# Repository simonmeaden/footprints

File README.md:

# footprints
My KICAD footprint library

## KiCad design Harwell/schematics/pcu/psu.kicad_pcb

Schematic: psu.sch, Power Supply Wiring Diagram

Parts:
C1: 2.2uF; CP_Elec_6.3x7.7
C2, C11, C13, C21: 2.2uF; C_0805
C3: 6800pF; C_0805
C4, C18, C24: 0.1uF; C_0805
C5: 3900pF; C_0805
C6, C14: 150uF; CP_Elec_6.3x7.7
C7, C9, C10, C15, C16, C23, C29: 0.01uF; C_0805
C8, C17: TBD; C_0805
C12: 22uF; C_0805
C19: 3300pF; C_0805
C20: 2200pF; C_0805
C25, C31: 100uF; CP_Tantalum_Case-X_EIA-7343-43_Reflow
C26, C36: 10uF; CP_Tantalum_Case-B_EIA-3528-21_Reflow
C27, C37: 1uF; CP_Tantalum_Case-A_EIA-3216-18_Reflow
C32: 22uF Tantalum; CP_Tantalum_Case-B_EIA-3528-21_Reflow
D1: MBR630; D_SOD-123
D2: MBR530; D_SOD-123
JP5: Jumper 5; SOLDER-JUMPER_2-WAY
L1, L2: 4uH; Inductor_Murata_3900_Series
L3, L4: 100uH; Inductor_TDK_VLCF5020_Series
L6: 22uH; Inductor_TDK__SLF_Series
M4: B240
Q1, Q6: FDS6612A
Q2, Q3, Q4, Q5: FDS6690AS
R1, R16: 15R; R_0805
R2, R3, R4, R17: 100K; R_0805
R5: 49K7; R_0805
R6: 1K8; R_0805
R7, R13: 330R; R_0805
R8, R12: 10K; R_0805
R9, R11: 18K2; R_0805
R10: 3R92; R_0805
R14: 2K7; R_0805
R15: 28K8; R_0805
R31: 20R; Potentiometer_Bourns_3362P
SKT1: CONN_01X02; CTBP9558_2AO
SKT2: LM2N_3.5_16; LM2N_16_2
TP1, TP2, TP3, TP4, TP5, TP6, TP7: TEST; Measurement_Point_Square-TH_Big
U3: MAX743; SO-16-W; Part Number IC000005
U5: CAT4139; TSOT-23-5; Part Number IC000007
U$3: TPD51020; TSSOP30

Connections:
+3V3: C14.1, C15.1, C20.2, L2.2, R15.2, SKT2.5, SKT2.6, SKT2.7, SKT2.8, TP4.1, U$3.11 (VO2)
+5V: C3.1, C6.1, C7.1, C24.1, C32.1, C36.1, JP5.3 (G3), L1.2, L3.1, L6.1, R5.1, SKT2.1, SKT2.2, SKT2.3, SKT2.4, TP2.1, U3.3 (AV+), U3.4 (V+), U3.5 (V+), U3.12 (V+), U3.13 (V+), U5.4 (~SHDN~), U5.5 (VIN), U$3.5 (VO1_VDDQ), U$3.21 (REG5_IN)
/DCIN: C1.1, C2.1, C12.1, C21.2, Q1.D, Q6.D, R2.1, R3.1, R4.1, R10.2, SKT1.1, TP1.1
/GND+12V: C31.2, D2.2 (A), SKT2.10, TP6.1, U3.9 (FB-)
/LL1: C4.1, L1.1, Q1.S, Q2.D, Q3.D, U$3.28 (LL1)
/LL2: C18.2, L2.1, Q4.D, Q5.D, Q6.S, U$3.18 (LL2)
/N$54: Q2.G, Q3.G, U$3.27 (OUT1_D)
/N$58: Q4.G, Q5.G, U$3.19 (OUT2_D)
/OUT1_U: Q1.G, R1.2
/OUT2_U: Q6.G, R16.2
/VDD+12.0: C25.1, D1.1 (K), SKT2.9, TP5.1, U3.16 (FB+)
/VDDLCD+: C37.1, M4.C, SKT2.11, TP7.1
GND: C1.2, C2.2, C6.2, C7.2, C9.1, C10.1, C11.2, C12.2, C13.1, C14.2, C15.2, C16.1, C21.1, C23.2, C24.2, C25.2, C26.2, C27.2, C29.2, C31.1, C32.2, C36.2, C37.2, JP5.1 (G1), L4.2, Q2.S, Q3.S, Q4.S, Q5.S, R8.1, R12.1, R31.2, SKT1.2, SKT2.12, SKT2.13, SKT2.14, SKT2.15, SKT2.16, TP3.1, U3.2 (AGND), U3.14 (GND), U5.2 (GND), U$3.4 (~SKIP~), U$3.7 (GND), U$3.20 (OUTGND2), U$3.26 (OUTGND1)
unnamed: C3.2, R7.1
unnamed: C4.2, U$3.30 (VBST1)
unnamed: C5.1, R5.2, R7.2, R8.2, U$3.1 (INV1)
unnamed: C5.2, R6.1
unnamed: C8.1, R9.1, U$3.25 (TRIP1)
unnamed: C9.2, U$3.3 (SSTRT1)
unnamed: C10.2, U$3.8 (REF_X)
unnamed: C8.2, C11.1, C17.2, R9.2, R10.1, R11.2, U$3.24 (VIN)
unnamed: C13.2, R17.2, U$3.22 (VREG5)
unnamed: C16.2, U$3.13 (SSTRT2)
unnamed: C17.1, R11.1, U$3.23 (TRIP2)
unnamed: C18.1, U$3.16 (VBST2)
unnamed: C19.1, R12.2, R13.1, R15.1, U$3.15 (INV2)
unnamed: C19.2, R14.1
unnamed: C20.1, R13.2
unnamed: C23.1, U3.1 (CC+)
unnamed: C26.1, U3.6 (VREF)
unnamed: C27.1, U3.7 (SS)
unnamed: C29.1, U3.8 (CC-)
unnamed: D1.2 (A), L3.2, U3.15 (LX+)
unnamed: D2.1 (K), L4.1, U3.10 (LX-)
unnamed: JP5.2 (G2), U3.11 (12/~15~)
unnamed: L6.2, M4.A, U5.1 (SW)
unnamed: R1.1, U$3.29 (OUT1_U)
unnamed: R2.2, U$3.10 (ENBL2)
unnamed: R3.2, U$3.9 (ENBL1)
unnamed: R4.2, U$3.6 (~DDR~)
unnamed: R6.2, U$3.2 (COMP1)
unnamed: R14.2, U$3.14 (COMP2)
unnamed: R16.1, U$3.17 (OUT2_U)
unnamed: R17.1, U$3.12 (PGOOD)
unnamed: R31.1, U5.3 (FB)

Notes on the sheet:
∓12V @ 125mA.Supply for DAC Buffer ampifier to avoid output Signal approaching either power rail.
Resistor R18 sets output voltage. 9.3V = 13R7
For Display LED Backlight.
Primary 5.0V & 3.3V Power supply.
DAC Buffer amp PSU
Display Backlight PSU
JP5 : 2-3 Connect for +12V 1-2 Connect for +15V

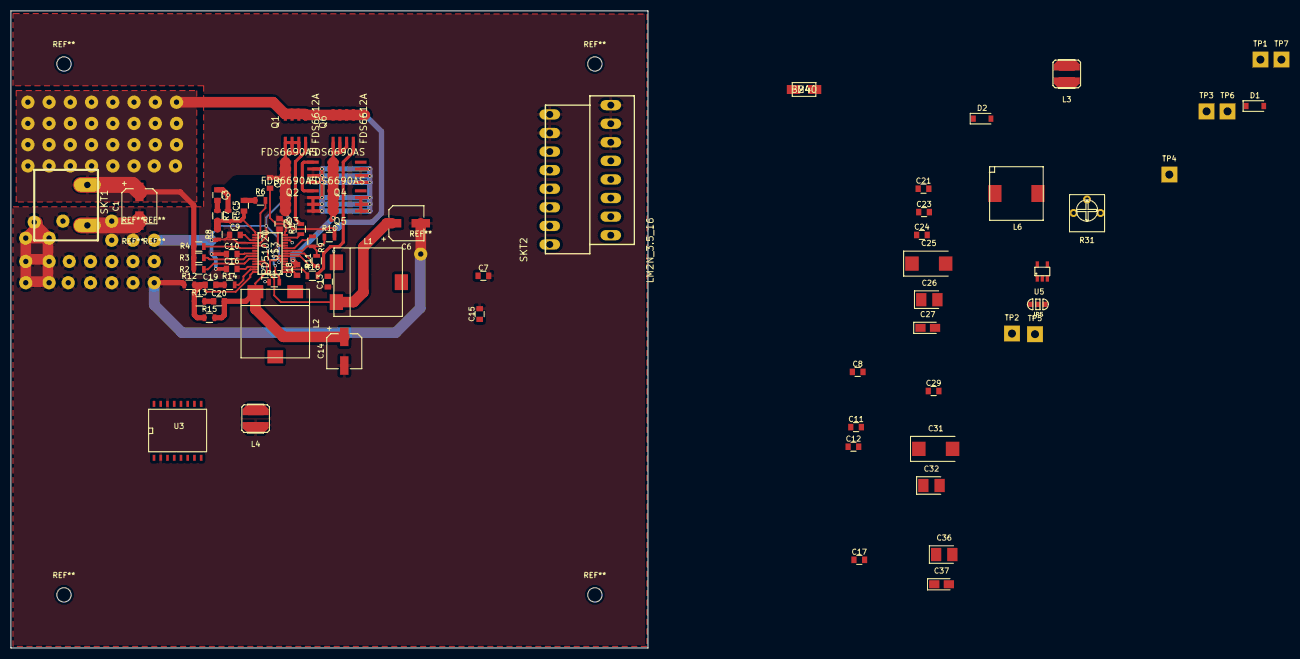
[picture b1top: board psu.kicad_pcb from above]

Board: 4 copper layers, 120.0 x 120.0 mm, 76 parts (0 on the bottom side), 43 nets.

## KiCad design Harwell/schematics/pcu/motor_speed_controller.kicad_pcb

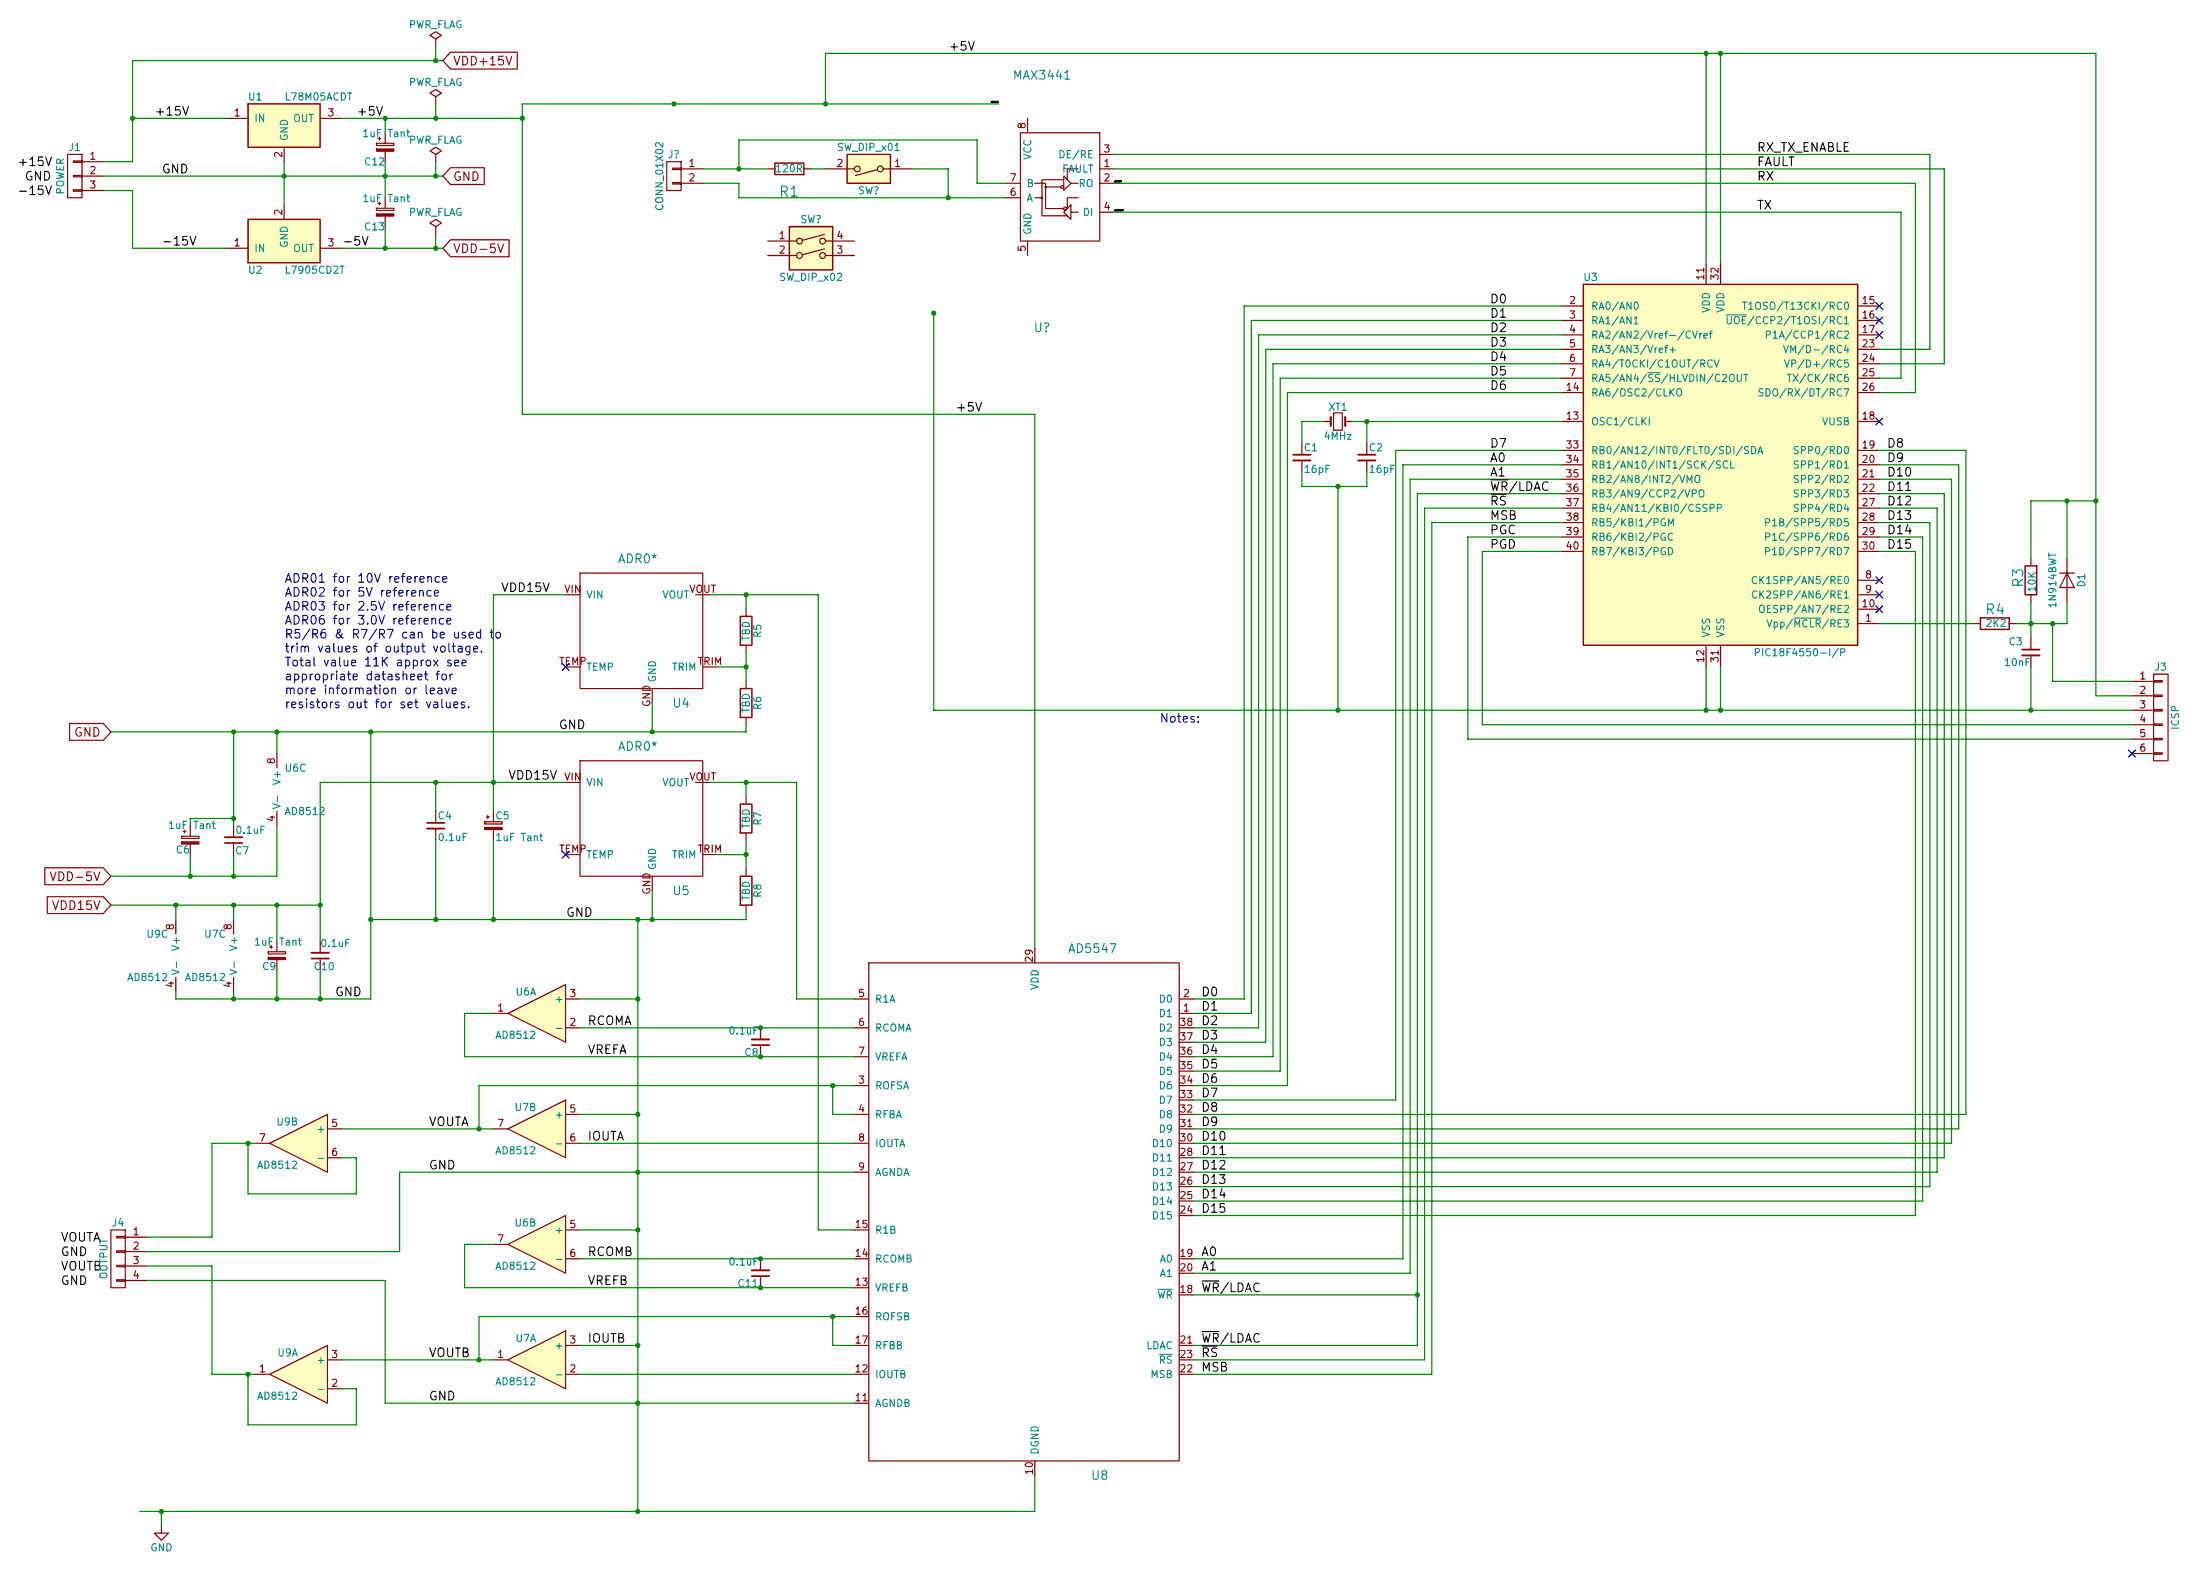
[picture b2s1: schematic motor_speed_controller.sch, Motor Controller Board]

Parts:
C1, C2: 16pF; C_0805
C3: 10nF; C_0805
C4, C7, C8, C10, C11: 0.1uF; C_0805
C5, C6, C9, C12, C13: 1uF Tant; CP_Tantalum_Case-A_EIA-3216-18_Reflow
D1: 1N914BWT; D_SOD-523F
J1: POWER; CTBP9558_3AO
J3: ICSP; Molex_KK_6373-06_06x2.54mm_Straight
J4: OUTPUT; CTBP9558_4AO
R1: 120R; R_0805
R3: 10K; R_0805
R4: 2K2; R_0805
R5, R6, R7, R8: TBD; R_0805
U1: L78M05ACDT; TO-252-2Lead_L778M05ACDT
U2: L7905CD2T; TO-252-2Lead_L7905CD2T
U3: PIC18F4550-I/P; DIP-40_W15.24mm
U4, U5: ADR0*; TSOT-5-ADR0*
U6, U7: AD8512; SOIC-8-N
U8: AD5547; TSSOP38
U9: AD8512
XT1: 4MHz; Crystal_IQD_HC49-4HSMX

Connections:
/+5V: C12.1, D1.1 (K), J3.2, R3.2, U1.3 (OUT), U3.11 (VDD), U3.32 (VDD), U8.29 (VDD); also elsewhere on the board
/-15V: J1.3, U2.1 (IN)
/A0: U3.34 (RB1/AN10/INT1/SCK/SCL), U8.19 (A0)
/A1: U3.35 (RB2/AN8/INT2/VMO), U8.20 (A1)
/D0: U3.2 (RA0/AN0), U8.2 (D0)
/D1: U3.3 (RA1/AN1), U8.1 (D1)
/D2: U3.4 (RA2/AN2/Vref-/CVref), U8.38 (D2)
/D3: U3.5 (RA3/AN3/Vref+), U8.37 (D3)
/D4: U3.6 (RA4/T0CKI/C1OUT/RCV), U8.36 (D4)
/D5: U3.7 (RA5/AN4/~SS~/HLVDIN/C2OUT), U8.35 (D5)
/D6: U3.14 (RA6/OSC2/CLKO), U8.34 (D6)
/D7: U3.33 (RB0/AN12/INT0/FLT0/SDI/SDA), U8.33 (D7)
/D8: U3.19 (SPP0/RD0), U8.32 (D8)
/D9: U3.20 (SPP1/RD1), U8.31 (D9)
/D10: U3.21 (SPP2/RD2), U8.30 (D10)
/D11: U3.22 (SPP3/RD3), U8.28 (D11)
/D12: U3.27 (SPP4/RD4), U8.27 (D12)
/D13: U3.28 (P1B/SPP5/RD5), U8.26 (D13)
/D14: U3.29 (P1C/SPP6/RD6), U8.25 (D14)
/D15: U3.30 (P1D/SPP7/RD7), U8.24 (D15)
/DATAIN: U3.26 (SDO/RX/DT/RC7); also elsewhere on the board
/DATAOUT: U3.25 (TX/CK/RC6); also elsewhere on the board
/IOUTA: U7.6 (-), U8.8 (IOUTA)
/MSB: U3.38 (RB5/KBI1/PGM), U8.22 (MSB)
/N$9: R1.2; also elsewhere on the board
/N$16: R1.1; also elsewhere on the board
/PGC: J3.5, U3.39 (RB6/KBI2/PGC)
/PGD: J3.4, U3.40 (RB7/KBI3/PGD)
/RCOMA: C8.2, U6.2 (-), U8.6 (RCOMA)
/RCOMB: C11.2, U6.6 (-), U8.14 (RCOMB)
/RX_ENABLE: U3.24 (VP/D+/RC5); also elsewhere on the board
/TX_ENABLE: U3.23 (VM/D-/RC4); also elsewhere on the board
/VOUTA: J4.1, U7.7, U8.3 (ROFSA), U8.4 (RFBA), U9.5 (+), U9.6 (-), U9.7
/VOUTB: J4.3, U7.1, U8.16 (ROFSB), U8.17 (RFBB), U9.1, U9.2 (-), U9.3 (+)
/VREFA: C8.1, U6.1, U8.7 (VREFA)
/VREFB: C11.1, U6.7, U8.13 (VREFB)
/~RS~: U3.37 (RB4/AN11/KBI0/CSSPP), U8.23 (~RS~)
/~WR~/LDAC: U3.36 (RB3/AN9/CCP2/VPO), U8.18 (~WR~), U8.21 (LDAC)
unnamed: C1.1, XT1.1
unnamed: C2.1, U3.13 (OSC1/CLKI), XT1.2
unnamed: C3.1, D1.2 (A), J3.1, R3.1, R4.1
unnamed: R4.2, U3.1 (Vpp/~MCLR~/RE3)
unnamed: R5.1, U4.VOUT, U8.15 (R1B)
unnamed: R5.2, R6.1, U4.TRIM
unnamed: R7.1, U5.VOUT, U8.5 (R1A)
unnamed: R7.2, R8.1, U5.TRIM
unnamed: U7.2 (-), U8.12 (IOUTB)
VDD15V: C4.1, C5.1, C9.1, C10.2, U4.VIN, U5.VIN, U7.8 (V+), U9.8 (V+)
VDD+15V: J1.1, U1.1 (IN)
VDD-5V: C6.2, C7.1, C13.2, U2.3 (OUT), U6.4 (V-)

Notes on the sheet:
Notes:
ADR01 for 10V reference ADR02 for 5V reference ADR03 for 2.5V reference ADR06 for 3.0V reference R5/R6 & R7/R7 can be used to trim values of output voltage. Total value 11K approx see appropriate datasheet for more information or leave resistors out for set values.

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
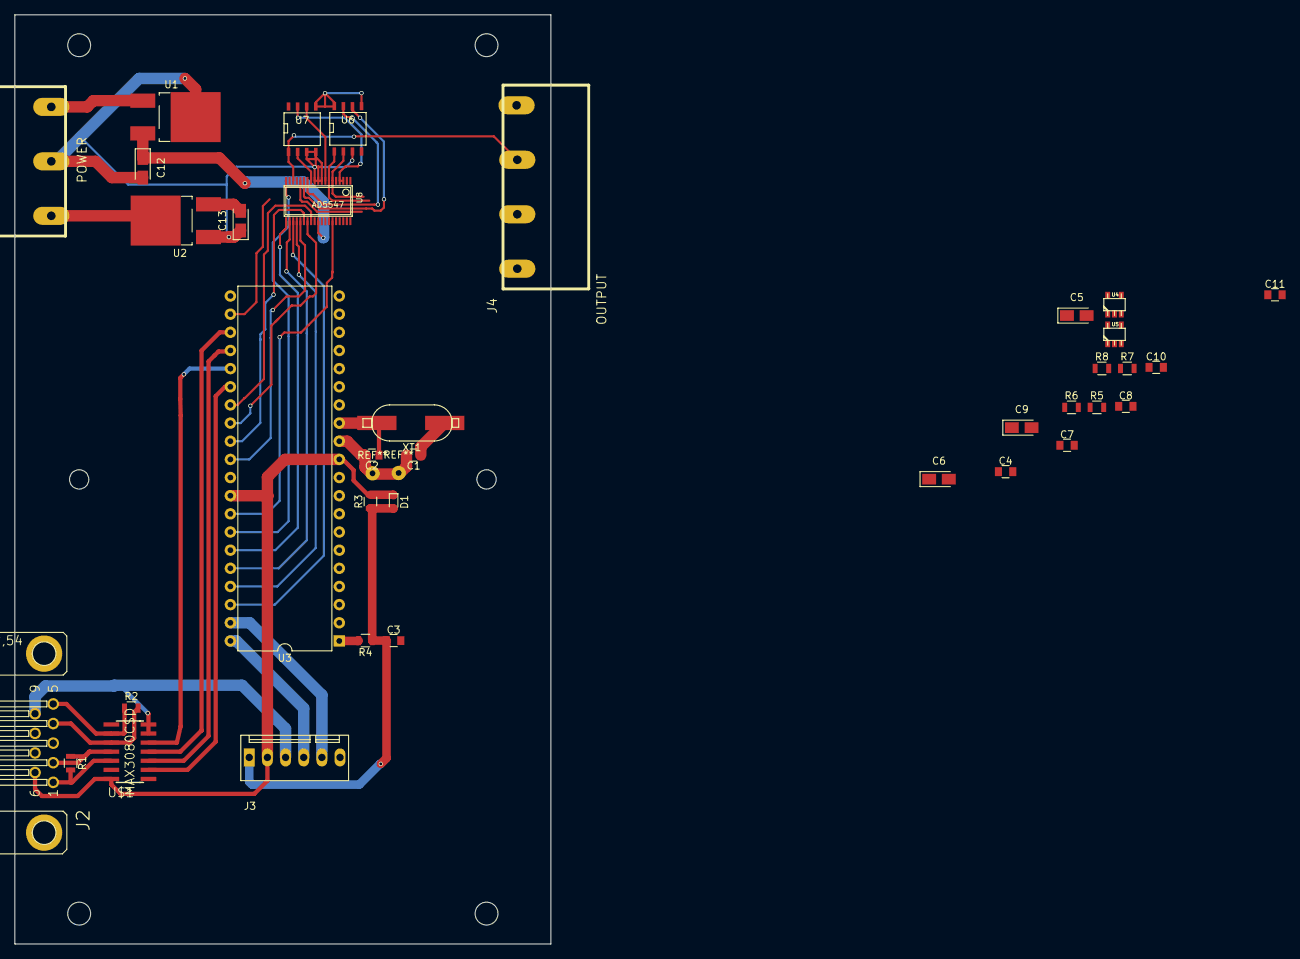
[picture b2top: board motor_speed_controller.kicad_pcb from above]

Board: 2 copper layers, 75.0 x 130.0 mm, 36 parts (0 on the bottom side), 53 nets.

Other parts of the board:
J2: RS485; F09HP
R2: 120R; R_0805
U$1: MAX3080CSD; SO14

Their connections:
/+5V: J2.6, U$1.14; also elsewhere on the board
/DATAIN: U$1.2; also elsewhere on the board
/DATAOUT: U$1.5; also elsewhere on the board
/N$9: J2.1, U$1.12; also elsewhere on the board
/N$16: J2.2, U$1.11; also elsewhere on the board
/N$17: J2.4, R2.2, U$1.10
/N$18: J2.5, R2.1, U$1.9
/RX_ENABLE: U$1.3; also elsewhere on the board
/TX_ENABLE: U$1.4; also elsewhere on the board

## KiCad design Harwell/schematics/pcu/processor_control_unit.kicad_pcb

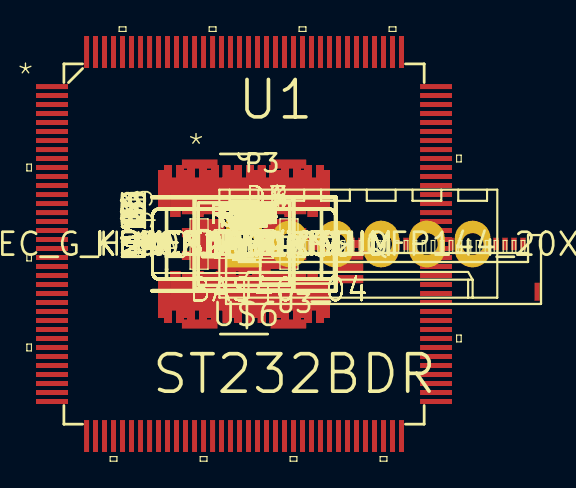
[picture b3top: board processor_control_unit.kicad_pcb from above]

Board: 2 copper layers, 219 parts (0 on the bottom side), 166 nets, no tracks yet.

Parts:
C4, C5: 18pF; C_0603
C6, C7, C8, C10, C11, C12, C13, C14: 0.1uF; C_0603
C9: 0.01uF; C_0603
D1, D2, D3, D4, D5: BAS40-04; SOT23
IC1, IC2, IC3, IC4, IC5, IC6, IC7, IC8: MCP23017SS; SSOP28
M1, M2, M3, M4, M5, M6, M7, M8, M9, M10, M11, M12, M13, M14, M15, M16: ACSL-6400; SO16
P1: CONN_01X32; 503480-3200
P3: CONN_01X06; Molex_KK-6410-06_06x2.54mm_Straight
R11, R12: 120R; R_0603
R17, R18, R19, R20, R25, R26, R27, R28, R49, R50, R51, R52, R57, R58, R59, R60, R133, R134, R135, R136, R141, R142, R143, R144, R165, R166, R167, R168, R173, R174, R175, R176, R197, R198, R199, R200, R205, R206, R207, R208, R229, R230, R231, R232, R237, R238, R239, R240, R261, R262, R263, R264, R269, R270, R271, R272, R293, R294, R295, R296, R301, R302, R303, R304: 147R; R_0805
R81, R83, R85, R90, R92, R94, R99, R101, R108, R110, R112, R117, R119, R123, R125, R325, R327, R329, R334, R336, R338, R343, R345, R352, R354, R356, R361, R363, R367, R369: 33K; R_0805
R82, R84, R86, R91, R93, R95, R100, R102, R104, R109, R111, R113, R118, R120, R124, R126, R326, R328, R330, R335, R337, R339, R344, R346, R348, R353, R355, R357, R362, R364, R368, R370: 3K3; R_0805
R87, R88, R89, R96, R97, R98, R105, R106, R107, R114, R115, R116, R121, R122, R127, R128, R331, R332, R333, R340, R341, R342, R349, R350, R351, R358, R359, R360, R365, R366, R371, R372: 10K; R_0805
R103, R347: R33K; R_0805
R129: 10K0; R_0805
R130: 1K0; R_0805
R131, R132: 2K7; R_0805
U1: ST232BDR; SOIC127P600X175-16N
U2, U4: CA3130; SOIC-8-N
U3: MCP47FEB22A0; TSSOP8
U9: PIC32MZXXXXEC_G_H_M_144-I_PLLQFP144_20X20MC-M; LQFP144_20X20MC-M
U$1, U$2, U$3, U$4: KEMET_AMAXIMUM; 3216-18W
U$5: MAX3080CSD; SO14
U$6: 2.2Uh; Inductor_Vishay_IHLP-2020BZ-11_Series

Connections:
/485-RX+: R11.2, U$5.12
/485-RX-: R11.1, U$5.11
/485-TX+: R12.2, U$5.10
/485-TX-: R12.1, U$5.9
/Analogue Inputs/AD0: D1.3, U9.36
/Analogue Inputs/AD1: D2.3, U9.35
/Analogue Inputs/AD2: D3.3, U9.34
/Analogue Inputs/AD3: D4.3, U9.31
/Analogue Inputs/AD4: D5.3, U9.26
/Dual DAC/LATCH/HVC: U3.6, U9.1
/INT-1: IC3.19, IC3.20, U9.79
/INT-2: IC5.19, IC5.20, U9.80
/INT-3: IC6.19, IC6.20, U9.106
/INT-4: IC7.19, IC7.20, U9.105
/Opto Isolated Inputs 1/CH0: IC3.21, M1.14
/Opto Isolated Inputs 1/CH1: IC3.22, M1.13
/Opto Isolated Inputs 1/CH2: IC3.23, M1.12
/Opto Isolated Inputs 1/CH3: IC3.24, M1.11
/Opto Isolated Inputs 1/CH4: IC3.25, M3.14
/Opto Isolated Inputs 1/CH5: IC3.26, M3.13
/Opto Isolated Inputs 1/CH6: IC3.27, M3.12
/Opto Isolated Inputs 1/CH7: IC3.28, M3.11
/Opto Isolated Inputs 1/CH11: IC3.4, M2.11
/Opto Isolated Inputs 1/CH13: IC3.6, M4.13
/Opto Isolated Inputs 1/CH14: IC3.7, M4.12
/Opto Isolated Inputs 1/CH15: IC3.8, M4.11
/Opto Isolated Inputs 2/CH0: IC5.21, M5.14
/Opto Isolated Inputs 2/CH1: IC5.22, M5.13
/Opto Isolated Inputs 2/CH2: IC5.23, M5.12
/Opto Isolated Inputs 2/CH3: IC5.24, M5.11
/Opto Isolated Inputs 2/CH4: IC5.25, M7.14
/Opto Isolated Inputs 2/CH5: IC5.26, M7.13
/Opto Isolated Inputs 2/CH6: IC5.27, M7.12
/Opto Isolated Inputs 2/CH7: IC5.28, M7.11
/Opto Isolated Inputs 2/CH11: IC5.4, M6.11
/Opto Isolated Inputs 2/CH13: IC5.6, M8.13
/Opto Isolated Inputs 2/CH14: IC5.7, M8.12
/Opto Isolated Inputs 2/CH15: IC5.8, M8.11
/Opto Isolated Inputs 3/CH0: IC6.21, M9.14
/Opto Isolated Inputs 3/CH1: IC6.22, M9.13
/Opto Isolated Inputs 3/CH2: IC6.23, M9.12
/Opto Isolated Inputs 3/CH3: IC6.24, M9.11
/Opto Isolated Inputs 3/CH4: IC6.25, M11.14
/Opto Isolated Inputs 3/CH5: IC6.26, M11.13
/Opto Isolated Inputs 3/CH6: IC6.27, M11.12
/Opto Isolated Inputs 3/CH7: IC6.28, M11.11
/Opto Isolated Inputs 3/CH11: IC6.4, M10.11
/Opto Isolated Inputs 3/CH13: IC6.6, M12.13
/Opto Isolated Inputs 3/CH14: IC6.7, M12.12
/Opto Isolated Inputs 3/CH15: IC6.8, M12.11
/Opto Isolated Inputs 4/CH0: IC7.21, M13.14
/Opto Isolated Inputs 4/CH1: IC7.22, M13.13
/Opto Isolated Inputs 4/CH2: IC7.23, M13.12
/Opto Isolated Inputs 4/CH3: IC7.24, M13.11
/Opto Isolated Inputs 4/CH4: IC7.25, M15.14
/Opto Isolated Inputs 4/CH5: IC7.26, M15.13
/Opto Isolated Inputs 4/CH6: IC7.27, M15.12
/Opto Isolated Inputs 4/CH7: IC7.28, M15.11
/Opto Isolated Inputs 4/CH11: IC7.4, M14.11
/Opto Isolated Inputs 4/CH13: IC7.6, M16.13
/Opto Isolated Inputs 4/CH14: IC7.7, M16.12
/Opto Isolated Inputs 4/CH15: IC7.8, M16.11
/PMD5: U9.3, U9.4
/Processor Control Unit/232-RX: U1.12, U9.16
/Processor Control Unit/232-TX: U1.11, U9.15
/Processor Control Unit/232-~CTS~: U1.9, U9.23
/Processor Control Unit/232-~RTS~: U1.10, U9.14
/Processor Control Unit/485-RX: U9.62, U$5.5
/Processor Control Unit/485-TX: U9.61, U$5.2
/Processor Control Unit/485-~RE~: U9.8, U$5.3
/Processor Control Unit/MCLR: P3.1, R130.2, U9.20
/Processor Control Unit/PGEC: P3.5, U9.37
/Processor Control Unit/PGED: P3.4, U9.38
/SCL-1: IC1.12, IC2.12, IC3.12, IC4.12, IC5.12, IC6.12, IC7.12, IC8.12, R131.1, U3.7, U9.90, U9.96
/SDA-1: IC3.13, R132.1, U9.91, U9.95
/SDA-2: IC1.13, IC2.13, IC4.13, IC5.13, IC6.13, IC7.13, IC8.13, U3.8
/Transistor buffered output 1/T0: IC4.21, R87.1
/Transistor buffered output 1/T1: IC4.22, R96.1
/Transistor buffered output 1/T2: IC4.23, R105.1
/Transistor buffered output 1/T3: IC4.24, R114.1
/Transistor buffered output 1/T4: IC4.25, R121.1
/Transistor buffered output 1/T5: IC4.26, R127.1
/Transistor buffered output 1/T6: IC4.27, R88.1
/Transistor buffered output 1/T7: IC4.28, R97.1
/Transistor buffered output 1/T8: IC4.1, R106.1
/Transistor buffered output 1/T9: IC4.2, R115.1
/Transistor buffered output 1/T10: IC4.3, R122.1
/Transistor buffered output 1/T11: IC4.4, R128.1
/Transistor buffered output 1/T12: IC4.5, R89.1
/Transistor buffered output 1/T13: IC4.6, R98.1
/Transistor buffered output 1/T14: IC4.7, R107.1
/Transistor buffered output 1/T15: IC4.8, R116.1
/Transistor buffered output 2/T0: IC8.21, R331.1
/Transistor buffered output 2/T1: IC8.22, R340.1
/Transistor buffered output 2/T2: IC8.23, R349.1
/Transistor buffered output 2/T3: IC8.24, R358.1
/Transistor buffered output 2/T4: IC8.25, R365.1
/Transistor buffered output 2/T5: IC8.26, R371.1
/Transistor buffered output 2/T6: IC8.27, R332.1
/Transistor buffered output 2/T7: IC8.28, R341.1
/Transistor buffered output 2/T8: IC8.1, R350.1
/Transistor buffered output 2/T9: IC8.2, R359.1
/Transistor buffered output 2/T10: IC8.3, R366.1
/Transistor buffered output 2/T11: IC8.4, R372.1
/Transistor buffered output 2/T12: IC8.5, R333.1
/Transistor buffered output 2/T13: IC8.6, R342.1
/Transistor buffered output 2/T14: IC8.7, R351.1
/Transistor buffered output 2/T15: IC8.8, R360.1
GND: C4.1, C5.1, C6.2, C7.2, C8.1, C9.2, C10.1, C11.2, C12.2, C13.2, C14.2, D4.1, D5.1, IC1.10, IC1.16, IC2.15, IC3.10, IC3.15, IC3.17, IC4.10, IC4.15, IC4.16, IC5.10, IC5.17, IC6.10, IC6.15, IC7.10, IC8.10, M1.9, M1.16, M3.9, M3.16, M4.9, M4.16, M5.9, M5.16, M7.9, M7.16, M8.9, M8.16, M9.9, M9.16, M11.9, M11.16, M12.9, M12.16, M13.9, M13.16, M15.9, M15.16, M16.9, M16.16, P3.3, R25.2, R26.2, R27.2, R28.2, R141.2, R142.2, R143.2, R144.2, R205.2, R206.2, R207.2, R208.2, R269.2, R270.2, R271.2, R272.2, U1.15, U3.5, U9.17, U9.32, U9.42, U9.54, U9.63, U9.75, U9.89, U9.108, U9.123, U9.136, U$5.6, U$5.7
unnamed: C4.2, U9.72
unnamed: C5.2, U9.71
unnamed: C9.1, R129.1, R130.1
unnamed: D1.1, D2.1, D3.1
unnamed: M1.1, R17.1
unnamed: M1.3, R18.1
unnamed: M1.5, R19.1
unnamed: M1.7, R20.1
unnamed: M3.1, R49.1
unnamed: M3.3, R50.1
unnamed: M3.5, R51.1
unnamed: M3.7, R52.1
unnamed: M4.1, R57.1
unnamed: M4.3, R58.1
unnamed: M4.5, R59.1
unnamed: M4.7, R60.1
unnamed: M5.1, R133.1
unnamed: M5.3, R134.1
unnamed: M5.5, R135.1
unnamed: M5.7, R136.1
unnamed: M7.1, R165.1
unnamed: M7.3, R166.1
unnamed: M7.5, R167.1
unnamed: M7.7, R168.1
unnamed: M8.1, R173.1
unnamed: M8.3, R174.1
unnamed: M8.5, R175.1
unnamed: M8.7, R176.1
unnamed: M9.1, R197.1
unnamed: M9.3, R198.1
unnamed: M9.5, R199.1
unnamed: M9.7, R200.1
unnamed: M11.1, R229.1
unnamed: M11.3, R230.1
unnamed: M11.5, R231.1
unnamed: M11.7, R232.1
unnamed: M12.1, R237.1
unnamed: M12.3, R238.1
unnamed: M12.5, R239.1
unnamed: M12.7, R240.1
unnamed: M13.1, R261.1
unnamed: M13.3, R262.1
unnamed: M13.5, R263.1
unnamed: M13.7, R264.1
unnamed: M15.1, R293.1
unnamed: M15.3, R294.1
unnamed: M15.5, R295.1
unnamed: M15.7, R296.1
unnamed: M16.1, R301.1
unnamed: M16.3, R302.1
unnamed: M16.5, R303.1
unnamed: M16.7, R304.1
VDD3.3: C6.1, C7.1, C8.2, C10.2, C11.1, C12.1, C13.1, C14.1, D1.2, D2.2, D4.2, D5.2, M1.10, M1.15, M2.10, M2.15, M3.10, M3.15, M4.10, M4.15, M5.10, M5.15, M6.10, M6.15, M7.10, M7.15, M8.10, M8.15, M9.10, M9.15, M10.10, M10.15, M11.10, M11.15, M12.10, M12.15, M13.10, M13.15, M14.10, M14.15, M15.10, M15.15, M16.10, M16.15, P3.2, R17.2, R18.2, R19.2, R20.2, R49.2, R50.2, R51.2, R52.2, R57.2, R58.2, R59.2, R60.2, R129.2, R133.2, R134.2, R135.2, R136.2, R165.2, R166.2, R167.2, R168.2, R173.2, R174.2, R175.2, R176.2, R197.2, R198.2, R199.2, R200.2, R229.2, R230.2, R231.2, R232.2, R237.2, R238.2, R239.2, R240.2, R261.2, R262.2, R263.2, R264.2, R293.2, R294.2, R295.2, R296.2, R301.2, R302.2, R303.2, R304.2, U9.18, U9.33, U9.55, U9.64, U9.88, U9.107, U9.122, U9.137
VDD5.0: IC1.9, IC1.15, IC1.17, IC2.16, IC2.17, IC3.9, IC3.16, IC3.18, IC4.9, IC4.17, IC4.18, IC5.9, IC5.15, IC5.16, IC5.18, IC6.9, IC6.16, IC6.17, IC6.18, IC7.9, IC7.15, IC7.16, IC7.17, IC7.18, IC8.9, IC8.15, IC8.16, IC8.17, IC8.18, R131.2, R132.2, U1.16, U3.1, U3.2, U$5.14
VDD24.0: R81.1, R82.1, R83.1, R84.1, R85.1, R86.1, R90.1, R91.1, R92.1, R93.1, R94.1, R95.1, R99.1, R100.1, R101.1, R102.1, R103.1, R104.1, R108.1, R109.1, R110.1, R111.1, R112.1, R113.1, R117.1, R118.1, R119.1, R120.1, R123.1, R124.1, R125.1, R126.1, R325.1, R326.1, R327.1, R328.1, R329.1, R330.1, R334.1, R335.1, R336.1, R337.1, R338.1, R339.1, R343.1, R344.1, R345.1, R346.1, R347.1, R348.1, R352.1, R353.1, R354.1, R355.1, R356.1, R357.1, R361.1, R362.1, R363.1, R364.1, R367.1, R368.1, R369.1, R370.1
VDD+12.0: U2.7, U4.7
VDD-12.0: U2.4, U4.4

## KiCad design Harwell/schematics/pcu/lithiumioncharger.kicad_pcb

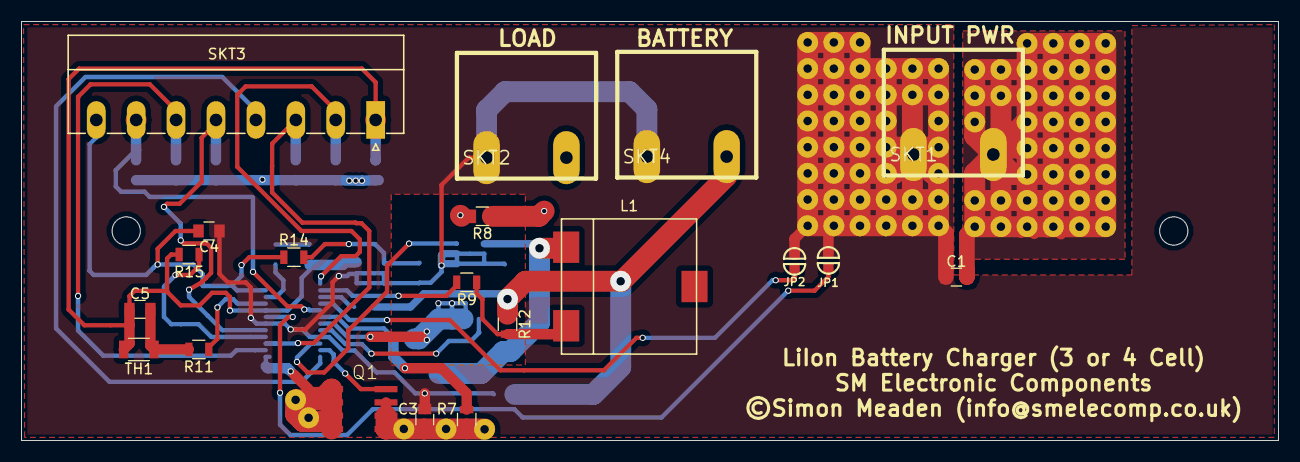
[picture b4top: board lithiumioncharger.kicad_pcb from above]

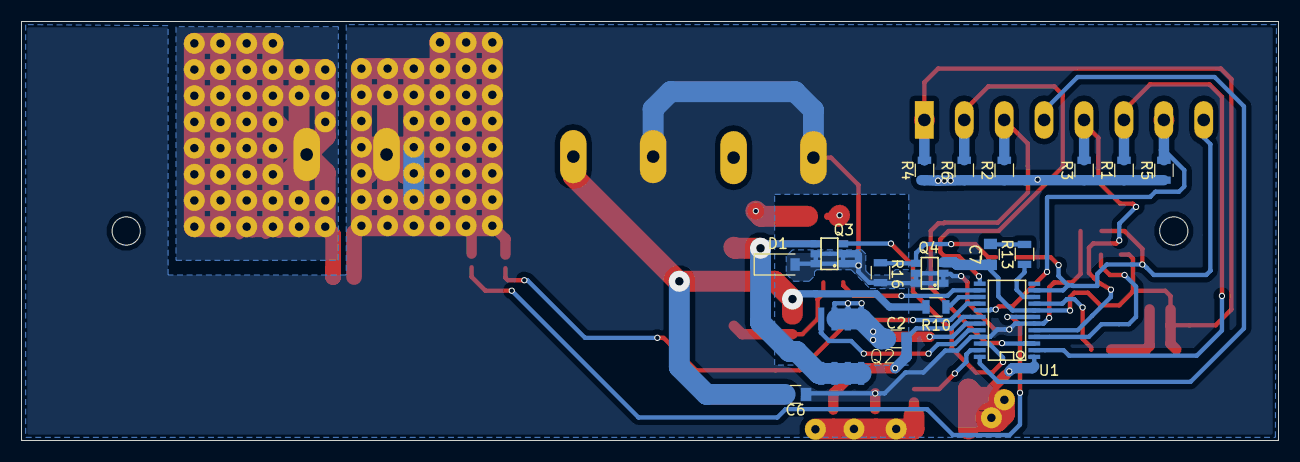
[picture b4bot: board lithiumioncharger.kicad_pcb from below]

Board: 4 copper layers, 120.0 x 40.0 mm, 37 parts (17 on the bottom side), 29 nets.

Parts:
C1: 0.1uF; C_0805
C2: 15nF; C_0805
C3, C6: 20uF; C_0805
C4: 0.0047uF; C_0805
C5: 0.47uF; C_0805
C7: 0.12uF; C_0805
D1: MBR530; D_SOD-123
JP1: Jumper 3; SOLDER-JUMPER_1-WAY
JP2: Jumper 4; SOLDER-JUMPER_1-WAY
L1: 15uH; Inductor_Murata_3900_Series
Q1, Q2: SI4431DY; Si4431CDY
Q3, Q4: FDC645
R1, R2, R3, R4, R5, R6: 100K; R_0805
R7: 4K99 1%; R_0805
R8, R12: 0R033 1%; R_0805
R9, R10: 3K01 1%; R_0805
R11: 32K4 1%; R_0805
R13: 6.04K 1%; R_0805
R14: 26.7K 1%; R_0805
R15: 309K 1%; R_0805
R16: 53K2 1%; R_0805
SKT1, SKT2, SKT4: CONN_01X02; CTBP9558_2AO
SKT3: CONN_01X08; PhoenixContact_MC-G_08x3.81mm_Angled
TH1: Thermistor 10K; R_1206
U1: LTC4007; SSOP-24

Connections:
/ACP: R2.2, SKT3.3, U1.3
/BAT: R10.2, U1.15
/BATTERY+: C6.2, R10.1, R12.1, SKT4.1
/BGATE: Q3.G, U1.22
/CLN: C2.1, Q2.S, R8.2, U1.19
/CLP: C2.2, R7.2, U1.18
/CSP: R9.2, U1.14
/DCIN: C1.2, Q1.D, R1.1, R2.1, R3.1, R4.1, R5.1, R6.1, SKT1.1, U1.1
/DCOUT: C3.2, Q1.S, R7.1, R8.1, SKT2.1
/FET_OUT: D1.1, L1.1, Q2.D, Q3.S
/GND: C1.1, C3.1, C4.1, C6.1, D1.2, JP1.2, JP2.2, Q3.D, Q4.D, R16.2, SKT1.2, SKT2.2, SKT4.2, U1.6, U1.21
/INFET: Q1.G, U1.23
/ITH: R13.1, U1.10
/PROG: C4.2, R14.1, SKT3.8, U1.11
/Q4_G: C5.1, C7.1, Q4.G, R4.2, R15.2, SKT3.1, TH1.2, U1.8
/SHDN: SKT3.4, U1.24
/TGATE: Q2.G, U1.20
/~CHG~: R1.2, SKT3.6, U1.2
/~FAULT~: R3.2, SKT3.5, U1.5
/~FLAG: R5.2, SKT3.7, U1.17
/~ICL~: R6.2, SKT3.2, U1.13
unnamed: C5.2, R11.2, TH1.1
unnamed: C7.2, R13.2
unnamed: JP1.1, U1.7
unnamed: JP2.1, U1.16
unnamed: L1.2, R9.1, R12.2
unnamed: Q4.S, R14.2, R16.1
unnamed: R11.1, U1.9
unnamed: R15.1, U1.4

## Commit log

2017-06-21 added files

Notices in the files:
Harwell/schematics/pcu/lithiumioncharger.kicad_pcb:
©Simon Meaden (info@smelecomp.co.uk)
Harwell/schematics/pcu/psu.sch:
Copyright © Simon Meaden
